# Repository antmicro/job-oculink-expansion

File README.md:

# Jetson Orin Baseboard OCuLink Expansion Board

Copyright (c) 2025 [Antmicro](https://www.antmicro.com)

## Overview

This project includes PCB design files for expansion card compatible with Antmicro's [Jetson Orin Baseboard](https://github.com/antmicro/jetson-orin-baseboard).
This expansion card exposes PCIe x2 break-routed from the Nvidia Jetson Orin Nano/NX SoM, and into an OCuLink-compliant connector.

The PCB design files were created with KiCad 9.x

## Key features

- Compatible with the [Jetson Orin Baseboard](https://github.com/antmicro/jetson-orin-baseboard)
- Exposes 2 lanes of PCIe 4.0 via an OCuLink connector
- Provides auxiliary PCIe signals

## Project structure

The main directory contains KiCad PCB project files and README.
The remaining files are stored in the following directories:

-   `img` - contains graphics for this README

## Licensing

This project is published under the [Apache-2.0](LICENSE) license.

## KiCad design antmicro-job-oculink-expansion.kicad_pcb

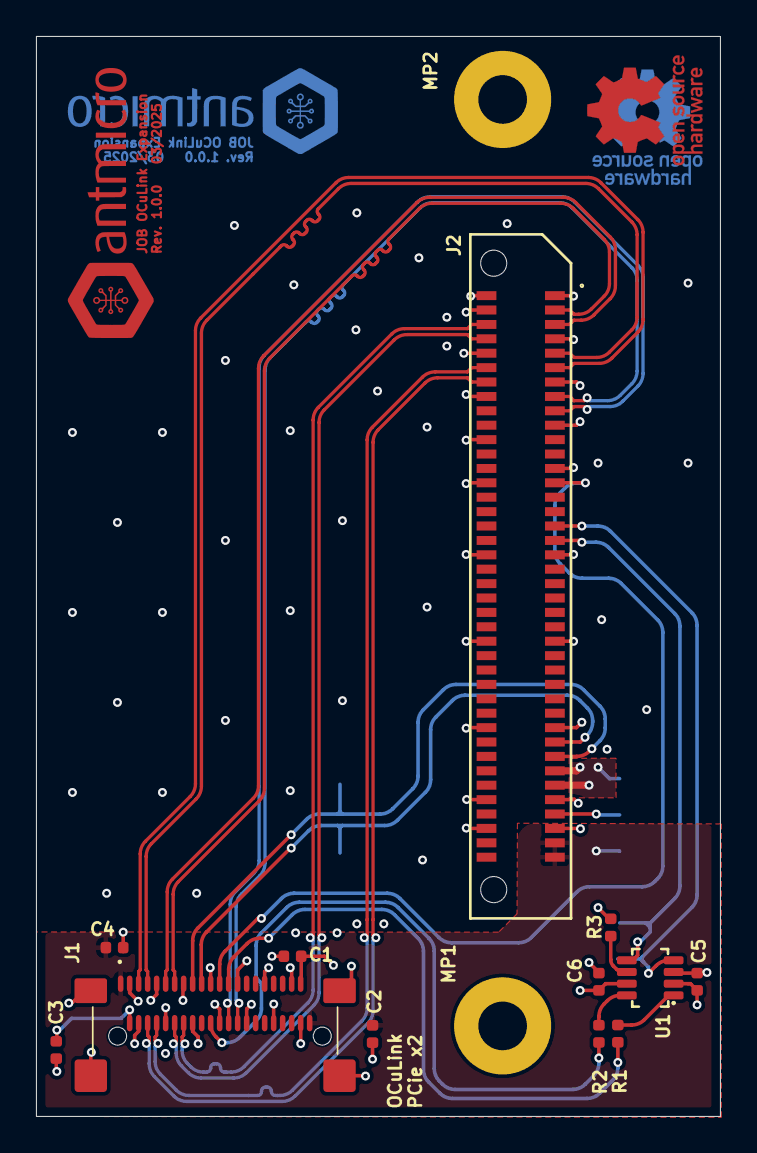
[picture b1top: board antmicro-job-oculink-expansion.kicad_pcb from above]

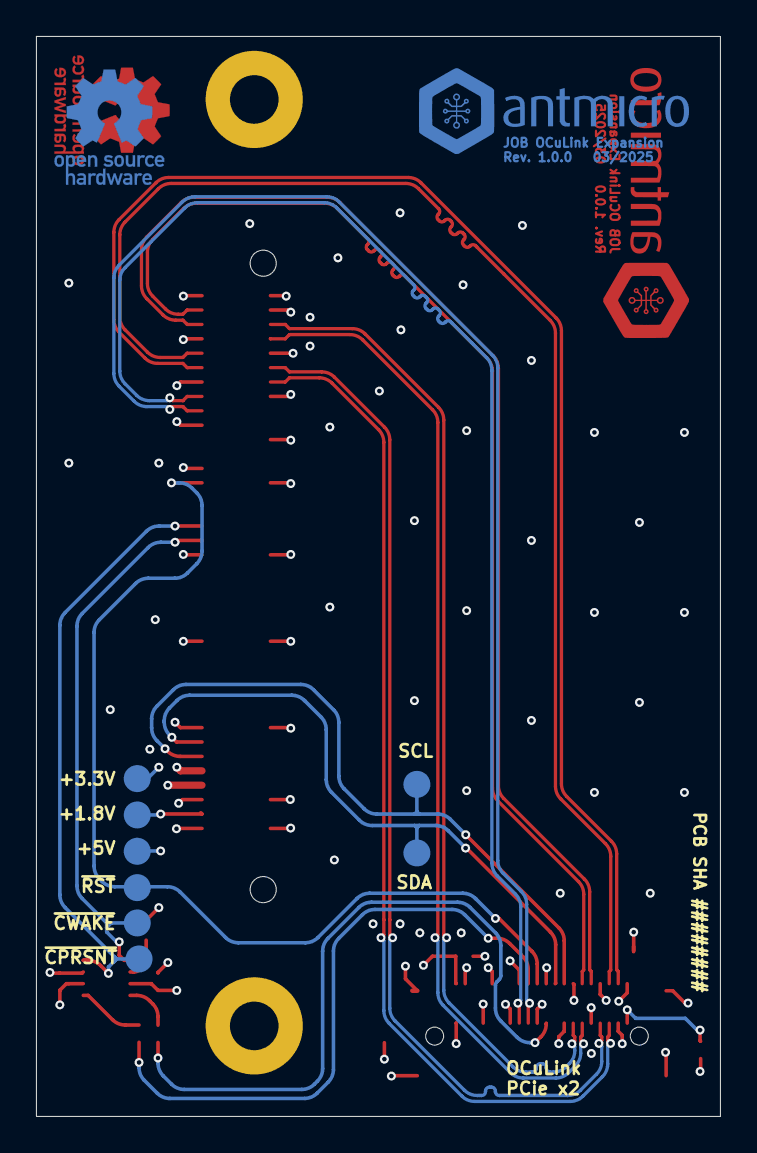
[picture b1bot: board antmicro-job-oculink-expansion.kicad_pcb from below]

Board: 4 copper layers, 38.0 x 60.0 mm, 26 parts (10 on the bottom side), 24 nets.

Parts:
C1, C2, C3, C4: C_10u_0402; C_0402_1005Metric
C5, C6: C_100n_0402; C_0402_1005Metric
J1: OCuLink_x4_Amphenol_G14A421211112HR; Amphenol_G14A421211112HR
J2: Plug_Samtec_ERM8_2x40_ERM8-040-05.0-L-DV-K-TR; Conn_Plug_Samtec_ERM8_2x40_ERM8-040-05.0-L-DV-K-TR
MP1, MP2: MP_Pad5.4mm_Drill2.7mm
N1, N3: oshw_logo; oshw-logo
N2, N4: antmicro_logo; antmicro-logo_scaled_15mm
R1, R2: R_0R_0402; R_0402_1005Metric
R3: R_10k_0402; R_0402_1005Metric
TP1, TP2, TP5, TP6, TP7, TP8, TP9, TP10: TP_1.5mm_SMD; TP_SMD_1.5mm
U1: MAX3373EEKA+; SOT-23-8

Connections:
+1V8: C5.2, J2.73, TP10.1, U1.3 (V_{L})
+3.3V: C1.2, C3.2, C6.2, J1.A1 (V_{ACT}_RX_3V3), J1.B21 (V_{ACT}_TX_3V3), J2.67, J2.69, TP8.1, U1.7 (V_{CC})
+5V: C2.2, C4.2, J1.A21 (5V), J1.B1 (5V), J2.77, J2.79, TP9.1
/I2C_SCL: J1.B9 (SCL), J2.65, TP1.1
/I2C_SDA: J1.B10 (SDA), J2.63, TP2.1
/JOB_GPIO07: J2.33, TP5.1, U1.4 (IO_V_{L}2)
/JOB_GPIO09: J2.35, TP6.1, U1.5 (IO_V_{L}1)
/PCIE_CLK+: J1.A12 (VSP1), J2.17
/PCIE_CLK-: J1.A13 (VSP2), J2.15
/PCIE_RX0+: J1.A3 (PER0+), J2.14
/PCIE_RX0-: J1.A4 (PER0-), J2.12
/PCIE_RX1+: J1.A6 (PER1+), J2.8
/PCIE_RX1-: J1.A7 (PER1-), J2.6
/PCIE_TX0+: J1.B3 (PET0+), J2.11
/PCIE_TX0-: J1.B4 (PET0-), J2.9
/PCIE_TX1+: J1.B6 (PET1+), J2.5
/PCIE_TX1-: J1.B7 (PET1-), J2.3
/~CPRSNT: R1.1, U1.1 (IO_V_{CC}2)
/~PCIE_CWAKE: R2.1, U1.8 (IO_V_{CC}1)
/~PCIE_RST: J1.B12 (~PERST), J2.27, TP7.1
GND: C1.1, C2.1, C3.1, C4.1, C5.1, C6.1, J1.A2 (GND), J1.A5 (GND), J1.A8 (GND), J1.A11 (GND), J1.A14 (GND), J1.A17 (GND), J1.A20 (GND), J1.B2 (GND), J1.B5 (GND), J1.B8 (GND), J1.B11 (GND), J1.B14 (GND), J1.B17 (GND), J1.B20 (GND), J1.SH, J2.1, J2.2, J2.4, J2.7, J2.10, J2.13, J2.16, J2.19, J2.22, J2.25, J2.28, J2.37, J2.38, J2.49, J2.50, J2.61, J2.62, J2.71, J2.72, J2.75, J2.76, MP1.1, MP2.1, R3.1, U1.2 (GND)
unnamed: J1.B13 (~CPRSNT), R1.2
unnamed: J1.A10 (~CWAKE), R2.2
unnamed: R3.2, U1.6 (~THREE_STATE)

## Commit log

2025-03-10 [#74340] Add readme
2025-03-10 [#74340] Add project
2025-03-10 [#74340] Finished schematic
2025-03-10 [#74340] Component placement
2025-03-13 [#74340] Routing
2025-03-14 [#74340] Apply Fixes
2025-03-14 [#74340] Add stiching vias
2025-03-14 [#74340] Add Logo
2025-03-14 [#74340] Add PCB SHA
2025-03-17 [#74340] Schematic fixes
2025-03-17 [#74340] Rename project
2025-03-17 [#74340] Set DRC rules
2025-03-17 [#74340] Routing fixes
2025-03-18 [#74340] Finished applying fixes
2025-03-18 [#74340] Add CI
2025-03-18 [#74340] Add mounting hole
2025-03-18 [#74340] Exclude overlap errors
2025-03-18 [#74340] Minor cosmetic update of schematics
2025-03-21 [#74340] Fix RX lines fanout
2025-03-24 [#74340] Repour planes
2025-03-28 [#74340] Add .gitignore
2025-03-28 [#74340] Fix F.Cu power plane
2025-03-28 [#74340] Update component placement
2025-03-28 [#74340] Finalize layout and add GND plane stiching
2025-03-28 [#74340] Add logos on both sides of PCB
2025-03-28 [#74340] Add minor power plane adjustments
2025-04-28 [#74340] Add assets
2025-04-30 [#76297] Fix trace not rounded
2025-04-30 [#76297] Move vias outside of pads
2025-04-30 [#76297] Fix Antmicro logo footprint not matching schematic
2025-04-30 [#76297] Join redriver power traces into one
2025-04-30 [#76297] Round traces
2025-04-30 [#76297] Rename +3.3V to +3V3
2025-04-30 [#76297] Adjust traces and silkscreen
2025-04-30 [#76297] Put +3V3 plane under redrivers
2025-04-30 [#76297] Clean up unconnected traces
2025-04-30 [#76297] Fix I2C pull-up resistor value
2025-04-30 [#76297] Route redrivers on the PCB
2025-04-30 [#76297] Fix DRC errors
2025-04-30 [#76297] Fix traces
    - spacing of PCIe traces is consistent
    - sharp angles are avoided
    - via in pads are moved
2025-04-30 [#76297] Fix same redriver I2C addresses
    U1 is now accessible on I2C address 0x70 and U2 is accessible on address
    0x72.
2025-04-30 [#76297] Place redrivers on the PCB
2025-04-30 [#76297] Add redriver setting pin labels
2025-04-30 [#76297] Connect 1K pull-down to CPRSNT#
2025-04-30 [#76297] Reorder redriver PCIe lanes
2025-04-30 [#76297] Add PCIe redriver
2025-04-30 [#76297] Set netclass vias to 0.45/0.1 mm
2025-04-30 [#76297] Connect redriver PRSNT# to CPRSNT#
2025-04-30 [#76297] Add 0R to OCuLink SDA and SCL
2025-04-30 [#76297] Bump schematic revision to 1.1.0
2025-04-30 [#76297] Reroute CPRSNT#
2025-04-30 [#76297] Tune PCIe differential pair skew
2025-04-30 [#76297] Move PCIe traces away from plane boundary
2025-04-30 [#76297] Fix redriver config pins assigned to PCIe netclass
2025-04-30 [#76297] Add GND vias near PCIe high-speed transition
2025-04-30 [#76297] Bump PCB revision to 1.1.0
2025-04-30 [#76297] Update assets
2025-04-30 [#76814] Configure the redrivers
2025-04-30 [#76814] Update assets
2025-05-22 [#77839] Add e-fuses to schematic
2025-05-22 [#77839] Connect OCuLink power through 0R resistors
2025-05-22 [#77839] Route e-fuses
2025-05-22 [#77839] Add power flag to OCuLink 3V3 input
2025-05-23 [#77839] Route OCuLink power through In2 layer
2025-05-23 [#77839] Adjust silkscreen
2025-05-23 [#77839] Update PCB from schematic
2025-05-23 [#77839] Adjust 5V power plane
2025-05-23 [#77839] Fix date on F.Mask and B.Mask layers
2025-05-28 [#77839] Adjust schematic
2025-05-28 [#77839] Add ILIM resistor value text
2025-05-28 [#77839] Reroute OCuLink power
2025-05-28 [#77839] Decouple OCuLink power instead of generic power lanes
2025-05-28 [#77839] Reroute e-fuses in schematic
2025-05-29 [#77839] Adjust ISET resistors
2025-05-29 [#77839] Fix PCB issues
2025-05-29 [#77839] Round traces
2025-05-29 [#77839] Refill zones
2025-05-29 [#77839] Adjust R3 silkscreen
2025-05-29 [#77839] Update assets
2025-05-30 Updated schematic pdf
2025-07-08 [#80078] Add license
2025-07-08 [#80078] Bump CI template
2025-07-10 [#80078] Update README
    [#80078] Remove Setup section
2025-07-10 [#80078] Rename KiCad files
2025-07-10 [#80078] Update README image
    [#80078] Change README board image
2025-07-10 [#80078] README review
2025-07-11 [#80078] Remove assets
2025-07-11 README: Update description, introduce new naming for the board render
2025-07-14 [#80078] Add OHP badge
2025-07-14 Minor edits to the text for clarity, added some details that the readers/users might look for.

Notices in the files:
parts and their libraries:
License: Apache-2.0
